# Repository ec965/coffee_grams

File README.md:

# Coffee Grams
Dial in your coffee with an IoT scale.

## PCB
The pcb uses an ESP32 microcontroller.

## Website
The website is built on the LAMP stack. It allows users to manually input data, view previous data, or view data collected from the IoT scale.

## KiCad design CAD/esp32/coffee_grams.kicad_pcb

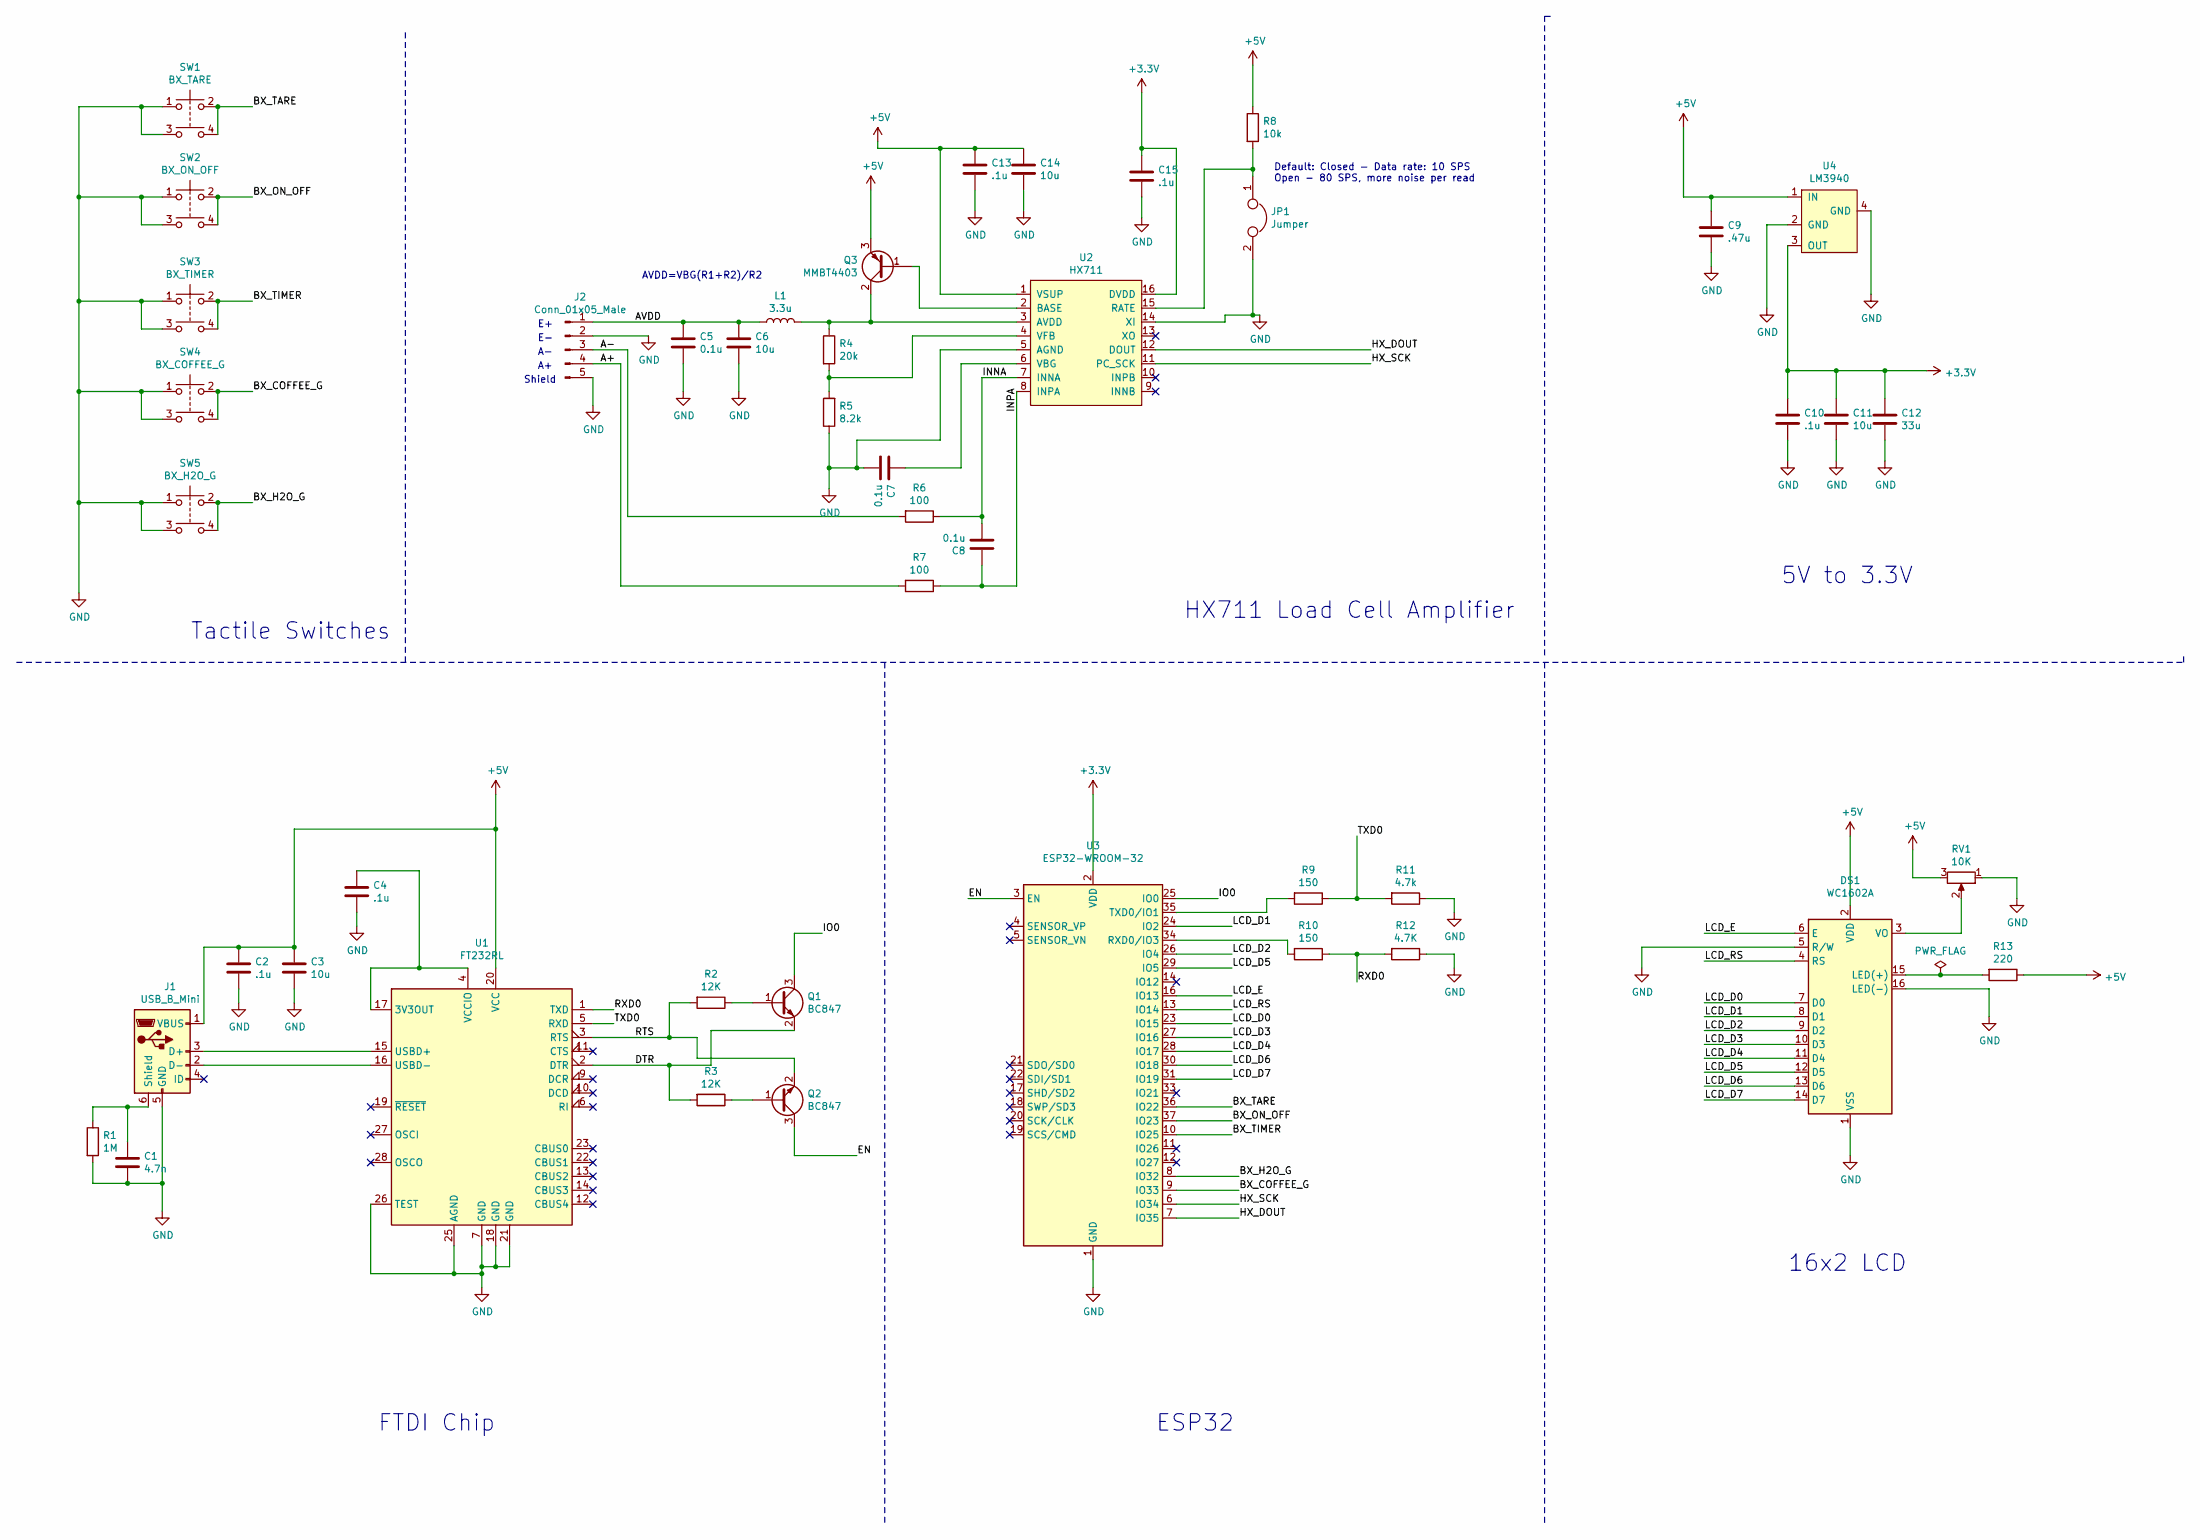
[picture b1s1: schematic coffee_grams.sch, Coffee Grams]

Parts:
C1: 4.7n; C_0805_2012Metric_Pad1.15x1.40mm_HandSolder
C2, C4, C10, C13, C15: .1u; C_0805_2012Metric_Pad1.15x1.40mm_HandSolder
C3, C6, C11, C14: 10u; C_0805_2012Metric_Pad1.15x1.40mm_HandSolder
C5, C7, C8: 0.1u; C_0805_2012Metric_Pad1.15x1.40mm_HandSolder
C9: .47u; C_0805_2012Metric_Pad1.15x1.40mm_HandSolder
C12: 33u; C_0805_2012Metric_Pad1.15x1.40mm_HandSolder
DS1: WC1602A
J1: USB_B_Mini; USB_Mini-B_Wuerth_65100516121_Horizontal
J2: Conn_01x05_Male; PinSocket_1x05_P2.54mm_Vertical
JP1: Jumper; SolderJumper-2_P1.3mm_Open_Pad1.0x1.5mm
L1: 3.3u; L_0805_2012Metric_Pad1.15x1.40mm_HandSolder
Q1, Q2: BC847; SOT-23
Q3: MMBT4403; SOT-23
R1: 1M; R_0805_2012Metric_Pad1.15x1.40mm_HandSolder
R2, R3: 12K; R_0805_2012Metric_Pad1.15x1.40mm_HandSolder
R4: 20k; R_0805_2012Metric_Pad1.15x1.40mm_HandSolder
R5: 8.2k; R_0805_2012Metric_Pad1.15x1.40mm_HandSolder
R6, R7: 100; R_0805_2012Metric_Pad1.15x1.40mm_HandSolder
R8: 10k; R_0805_2012Metric_Pad1.15x1.40mm_HandSolder
R9, R10: 150; R_0805_2012Metric_Pad1.15x1.40mm_HandSolder
R11: 4.7k; R_0805_2012Metric_Pad1.15x1.40mm_HandSolder
R12: 4.7K; R_0805_2012Metric_Pad1.15x1.40mm_HandSolder
R13: 220; R_0805_2012Metric_Pad1.15x1.40mm_HandSolder
RV1: 10K; Potentiometer_Bourns_3266W_Vertical
SW1: BX_TARE; SW_TH_Tactile_Omron_B3F-10xx
SW2: BX_ON_OFF; SW_TH_Tactile_Omron_B3F-10xx
SW3: BX_TIMER; SW_TH_Tactile_Omron_B3F-10xx
SW4: BX_COFFEE_G; SW_TH_Tactile_Omron_B3F-10xx
SW5: BX_H2O_G; SW_TH_Tactile_Omron_B3F-10xx
U1: FT232RL; SSOP-28_5.3x10.2mm_P0.65mm
U2: HX711; SOP-16_4.4x10.4mm_P1.27mm
U3: ESP32-WROOM-32
U4: LM3940; SOT-223

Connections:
+3V3: C10.1, C11.1, C12.1, C15.1, U2.16 (DVDD), U3.2 (VDD), U4.3 (OUT)
+5V: C2.1, C3.1, C9.1, C13.1, C14.1, DS1.2 (VDD), J1.1 (VBUS), Q3.3 (E), R8.1, R13.1, RV1.3, U1.20 (VCC), U2.1 (VSUP), U4.1 (IN)
/A+: J2.4, R7.2
/A-: J2.3, R6.2
/AVDD: C5.1, C6.1, J2.1, L1.1
/BX_COFFEE_G: SW4.2, SW4.4, U3.9 (IO33)
/BX_H2O_G: SW5.2, SW5.4, U3.8 (IO32)
/BX_ON_OFF: SW2.2, SW2.4, U3.37 (IO23)
/BX_TARE: SW1.2, SW1.4, U3.36 (IO22)
/BX_TIMER: SW3.2, SW3.4, U3.10 (IO25)
/DTR: Q1.2 (E), R3.2, U1.2 (DTR)
/EN: Q2.3 (C), U3.3 (EN)
/HX_DOUT: U2.12 (DOUT), U3.7 (IO35)
/HX_SCK: U2.11 (PC_SCK), U3.6 (IO34)
/INNA: C8.2, R6.1, U2.7 (INNA)
/INPA: C8.1, R7.1, U2.8 (INPA)
/IO0: Q1.3 (C), U3.25 (IO0)
/LCD_D0: DS1.7 (D0), U3.23 (IO15)
/LCD_D1: DS1.8 (D1), U3.24 (IO2)
/LCD_D2: DS1.9 (D2), U3.26 (IO4)
/LCD_D3: DS1.10 (D3), U3.27 (IO16)
/LCD_D4: DS1.11 (D4), U3.28 (IO17)
/LCD_D5: DS1.12 (D5), U3.29 (IO5)
/LCD_D6: DS1.13 (D6), U3.30 (IO18)
/LCD_D7: DS1.14 (D7), U3.31 (IO19)
/LCD_E: DS1.6 (E), U3.16 (IO13)
/LCD_RS: DS1.4 (RS), U3.13 (IO14)
/RTS: Q2.2 (E), R2.2, U1.3 (RTS)
/RXD0: R10.1, R12.2, U1.1 (TXD)
/TXD0: R9.1, R11.2, U1.5 (RXD)
GND: C1.2, C2.2, C3.2, C4.2, C5.2, C6.2, C7.2, C9.2, C10.2, C11.2, C12.2, C13.2, C14.2, C15.2, DS1.1 (VSS), DS1.5 (R/W), DS1.16 (LED(-)), J1.5 (GND), J2.2, J2.5, JP1.2, R1.2, R5.1, R11.1, R12.1, RV1.1, SW1.1, SW1.3, SW2.1, SW2.3, SW3.1, SW3.3, SW4.1, SW4.3, SW5.1, SW5.3, U1.7 (GND), U1.18 (GND), U1.21 (GND), U1.25 (AGND), U1.26 (TEST), U2.5 (AGND), U2.14 (XI), U3.1 (GND), U3.15 (GND), U3.38 (GND), U3.39 (GND), U4.2 (GND), U4.4 (GND)
unnamed: C1.1, J1.6 (Shield), R1.1
unnamed: C4.1, U1.4 (VCCIO), U1.17 (3V3OUT)
unnamed: C7.1, U2.6 (VBG)
unnamed: DS1.3 (VO), RV1.2
unnamed: DS1.15 (LED(+)), R13.2
unnamed: J1.2 (D-), U1.16 (USBD-)
unnamed: J1.3 (D+), U1.15 (USBD+)
unnamed: JP1.1, R8.2, U2.15 (RATE)
unnamed: L1.2, Q3.2 (C), R4.1, U2.3 (AVDD)
unnamed: Q1.1 (B), R2.1
unnamed: Q2.1 (B), R3.1
unnamed: Q3.1 (B), U2.2 (BASE)
unnamed: R4.2, R5.2, U2.4 (VFB)
unnamed: R9.2, U3.35 (TXD0/IO1)
unnamed: R10.2, U3.34 (RXD0/IO3)

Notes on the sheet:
Shield
AVDD=VBG(R1+R2)/R2
Default: Closed - Data rate: 10 SPS Open - 80 SPS, more noise per read
FTDI Chip
ESP32
16x2 LCD
5V to 3.3V
HX711 Load Cell Amplifier
Tactile Switches

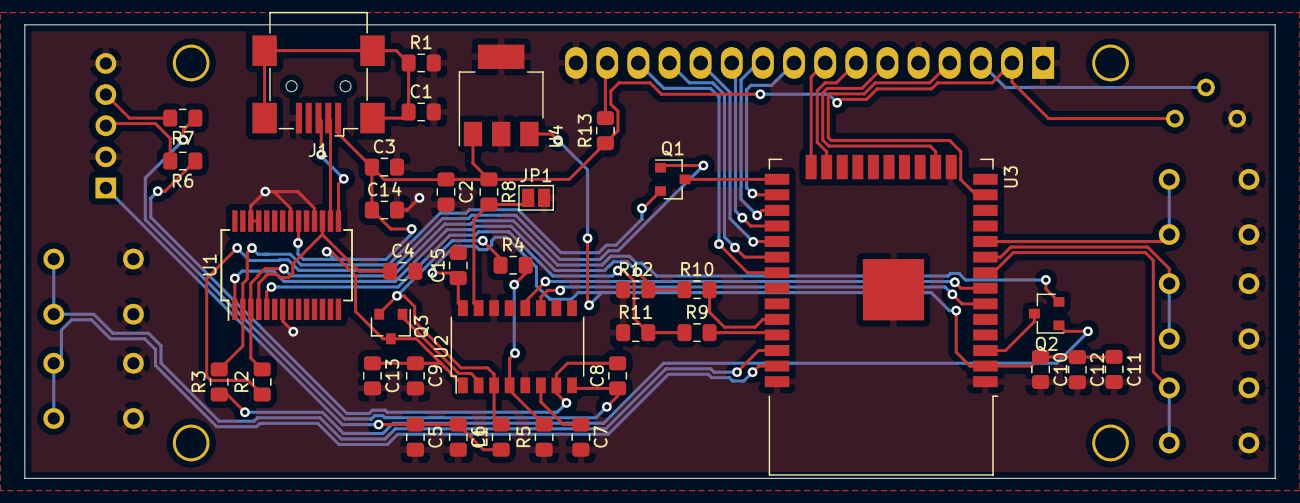
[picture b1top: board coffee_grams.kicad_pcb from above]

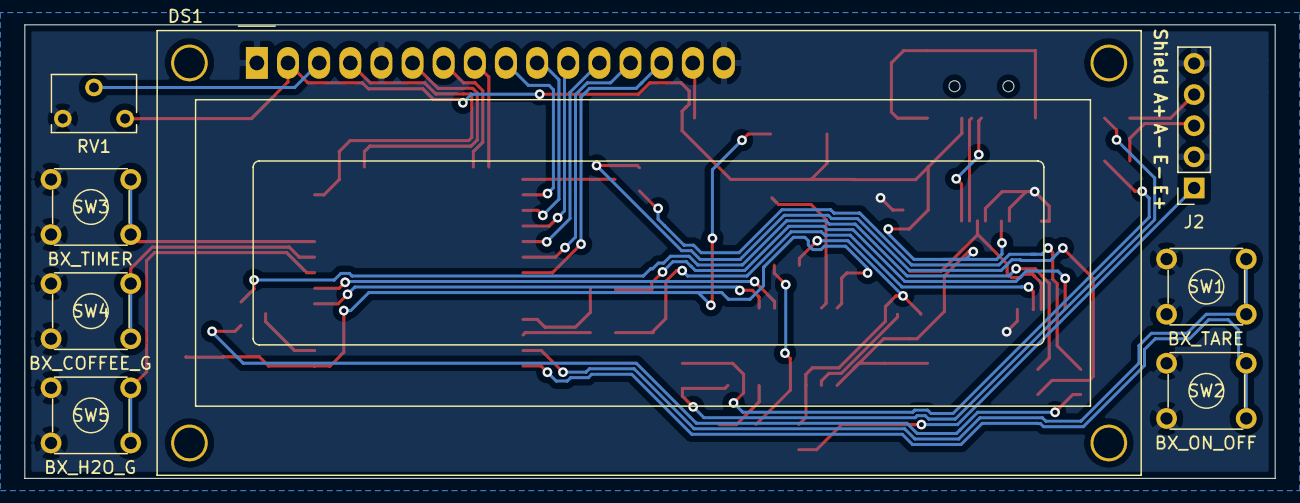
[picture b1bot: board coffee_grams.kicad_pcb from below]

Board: 2 copper layers, 102.0 x 37.0 mm, 46 parts (8 on the bottom side), 46 nets.

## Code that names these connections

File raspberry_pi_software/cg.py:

import mysql.connector
import time
import sys
import argparse
import RPi.GPIO as GPIO
from hx711 import HX711 #for raspberry pi 3b+ use pin 17 for 3v3, it seems to have much less noise than pin 1
import I2C_LCD_driver

#button macros
BX_on_off = 19
BX_tare = 13
BX_timer = 26
BX_coffee_g = 20
BX_water_g = 21

#button input states for event and callback
IN_on_off=False
IN_timer=False
IN_tare=False
IN_coffee_g=False
IN_water_g=False

#on off vars
onoff_state = False

#timer vars
start_time = 0
brew_time = 0
start_lock = False

#weight vars
coffee_g = 0
water_g = 0

#button callbacks
#use globals b/c callback is on a different thread
def CB_on_off (BX_on_off):
    global IN_on_off
    if args.verbose:
        print("BX_on_off pressed")
    IN_on_off=True

def CB_tare(BX_tare) :
    global IN_tare
    if args.verbose:
        print("BX_tare pressed")
    IN_tare = True

def CB_timer(BX_timer):
    global IN_timer
    if args.verbose:
        print("BX_timer pressed")
    IN_timer=True

def CB_coffee_g(BX_coffee_g):
    global IN_coffee_g
    if args.verbose:
        print("BX_coffee_g pressed")
    IN_coffee_g=True

def CB_water_g(BX_water_g):
    global IN_water_g
    if args.verbose:
        print("BX_water_g pressed")
    IN_water_g=True

if __name__ == "__main__":
    #arge parser
    parser = argparse.ArgumentParser(description='Dial in your coffee.',formatter_class=argparse.RawTextHelpFormatter)
    parser.add_argument("tool", help="What tool are you using to brew your coffee?\nm=melitta pour over\nfp=french press")
    parser.add_argument("coffee_type", help="What kind of coffee are you drinking?")
    parser.add_argument("-v", "--verbose", help="increase output verbosity",action="store_true")
    args = parser.parse_args()

    if args.tool == 'm' :
        tool_type="melittaPourOver"
    elif args.tool=='fp' :
        tool_type="frenchpress"
    else:
        print("invalid tool type")
        sys.exit()

    #set up buttons
    BX_list = [BX_tare,BX_on_off,BX_timer,BX_coffee_g,BX_water_g]
    CB_list = [CB_tare,CB_on_off,CB_timer,CB_coffee_g,CB_water_g]
    if args.verbose:
        print("setting up buttons")

    GPIO.setmode(GPIO.BCM)#basically the GPIO numbers instead of the physical pin numbers
    GPIO.setup(BX_list, GPIO.IN, pull_up_down=GPIO.PUD_UP)

    for CB,BX in zip(CB_list,BX_list) :
        GPIO.add_event_detect(BX,GPIO.FALLING,callback=CB,bouncetime=200)

    #set up hx711 & loadcell
    if args.verbose:
        print("setting up hx711 & loadcell")

    hx = HX711(5, 6)#DT to 5, SCK to 6 (BCM pins)
    hx.set_reading_format("MSB", "MSB")
    hx.set_reference_unit(-278)
    hx.reset()
    hx.tare()

    #set up lcd
    if args.verbose:
        print("setting up LCD")
    mylcd = I2C_LCD_driver.lcd()
    mylcd.lcd_clear()
    mylcd.backlight(0)

    if args.verbose:
        print("setup complete")

    while True :
        try:
            if IN_on_off:
                onoff_state = not onoff_state
                mylcd.lcd_clear()
                if onoff_state : #system is on
                    hx.power_up()
                    mylcd.backlight(1)
                    mylcd.lcd_display_string("Welcome to",1)
                    mylcd.lcd_display_string("Coffee Grams",2)
                else : #system is off
                    hx.power_down()
                    mylcd.backlight(0)

                    #reset variables
                    coffee_g = 0
                    water_g = 0
                    brew_time = 0
                    start_time = 0
                    start_lock = False

                IN_on_off=False

            if onoff_state :

                #update weight
                # if args.verbose:
                #     print("collecting weight samples")
                # current_weight=0
                # sample_size=4
                # for i in range(sample_size):
                #     current_weight+=hx.get_weight(5)
                # current_weight = current_weight/sample_size
                # current_weight = f"{current_weight:.2f}"

                current_weight = f"{hx.get_weight(5):.2f}"

                #User Interface
                # mylcd.lcd_clear()
                mylcd.lcd_display_string(f"Weight(g): {current_weight}         ",2)
                if args.verbose:
                    print(f"weight: {current_weight}")

                current_time = f"{time.strftime('%m-%d-%Y %H:%M:%S', time.localtime(time.time()))}"
                if start_lock :
                    current_time = f"Timer: {time.strftime('%M:%S', time.localtime(time.time()-start_time-57600))}    "#idk why it kept displaying 16 in the hours position

                mylcd.lcd_display_string(current_time,1)
                if args.verbose:
                    print(current_time)

                #timer start/stop
                if IN_timer:
                    if start_lock:
                        brew_time = time.strftime('%H:%M:%S', time.localtime(time.time() - start_time))
                        mylcd.lcd_display_string("Brew time saved ",1)
                        time.sleep(.5)
                        if args.verbose:
                            print(f"brew time: {brew_time}")
                    else:
                        start_time = time.time()
                    start_lock = not start_lock
                    IN_timer=False

                #tare scale
                if IN_tare:
                    hx.tare()
                    IN_tare=False
                    tare_str = "Scale Tared"
                    # mylcd.lcd_display_string(tare_str+"     ",2)
                    if args.verbose:
                        print(tare_str)

                #record weights
                if IN_coffee_g:
                    coffee_g = float(current_weight)
                    mylcd.lcd_display_string("coffee pushed   ",2)
                    time.sleep(.5)
                    if args.verbose:
                        print(f"coffee weight recorded: {coffee_g}")
                    IN_coffee_g=False


                if IN_water_g:
                    water_g = float(current_weight)
                    mylcd.lcd_display_string("water pushed    ",2)
                    time.sleep(.5)
                    if args.verbose:
                        print(f"water weight recorded: {water_g}")
                    IN_water_g=False

                ID_num = 1
                # coffee_g = 14.1
                water_g = 222.4
                # brew_time = "00:03:43"
                #
                if water_g and coffee_g and brew_time :
                    try :
                        db = mysql.connector.connect(user='coffee_grams_admin', password='well50',
                                                    host='localhost',
                                                    database='coffee_grams')
                        if args.verbose:
                            print("db opened")

                        cursor = db.cursor()

                        insert_stm = "INSERT INTO " + tool_type  + " (ID, datetime, coffee, water, brew_time, type) VALUES (%s, %s, %s, %s, %s, %s)"
                        #change the Database ID back to Auto increment and ID_num to NULL
                        data = (ID_num  ,time.strftime('%Y-%m-%d %H:%M:%S') , coffee_g , water_g , brew_time,args.coffee_type)

                        cursor.execute(insert_stm,data)

                        db.commit()

                        if args.verbose:
                            print("data inserted")

                    except mysql.connector.Error as e :
                        print("Error:",e)

                    finally :
                        coffee_g = 0
                        water_g = 0
                        brew_time = 0
                        if db.is_connected() :
                            db.close()
                            cursor.close()

                            if args.verbose:
                                print("db closed")

        except (KeyboardInterrupt, SystemExit):
            hx.power_down()
            mylcd.lcd_clear()
            mylcd.backlight(0)
            GPIO.cleanup()
            print("exiting")
            sys.exit()

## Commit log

2020-03-30 readme
2020-03-31 firmware
2020-03-31 remove hx711py git repo
2020-03-31 callback buttons
2020-05-19 PCB start
2020-05-20 completed schematic, started pcb
2020-05-20 completed 0.1 board
2020-05-20 create r-pi pcb files
2020-05-20 move rpi software files
2020-05-22 working php form
2020-05-23 update php to class
2020-05-25 dynamic table and chart
2020-05-25 js form validation
2020-05-26 validation error messages
2020-11-20 pcb rev2
2020-11-20 fix readme
